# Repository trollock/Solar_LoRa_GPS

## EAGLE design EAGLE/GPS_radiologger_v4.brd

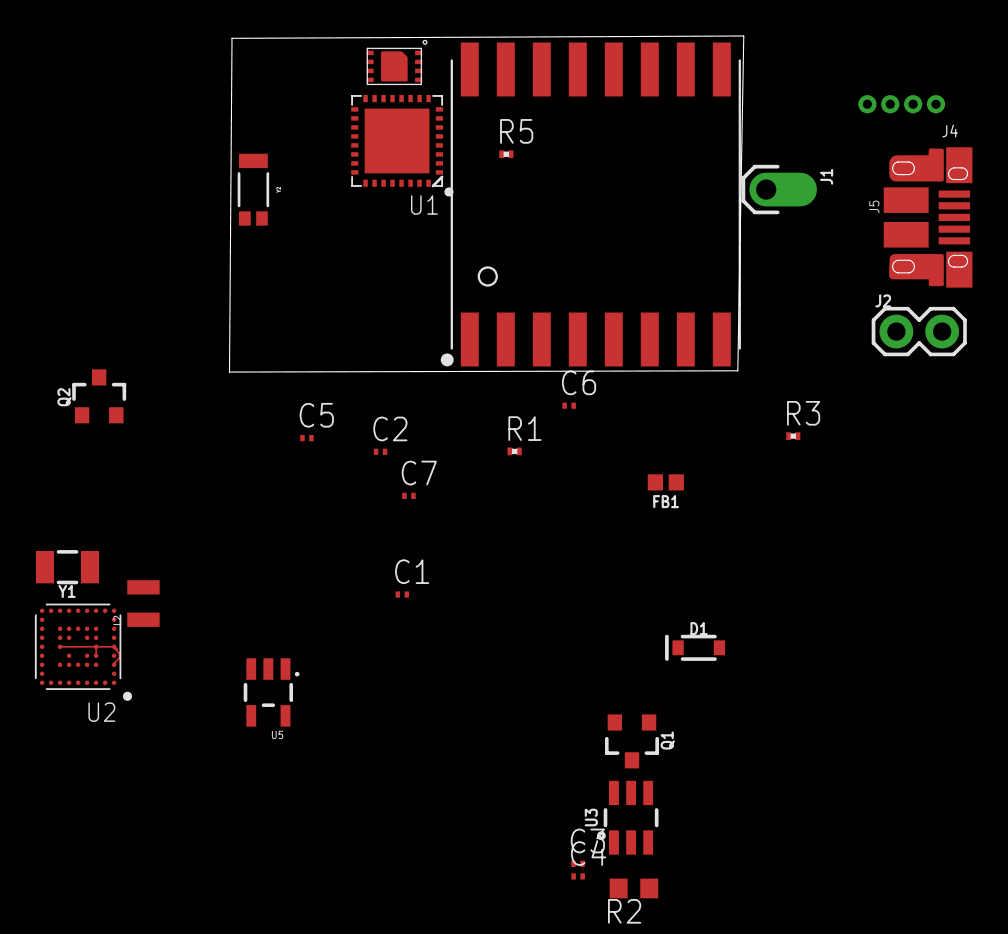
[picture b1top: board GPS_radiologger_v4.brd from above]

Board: 2 copper layers, 28 parts (0 on the bottom side), 30 nets.

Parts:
C1: 47 pF; C0201
C2, C3, C4: 10 uF; C0201
C5: 4.7 uF; C0201
C6: 0.1 uF; C0201
C7: 1 uF; C0201
D1: 1A/23V/620mV; SOD-323
FB1: FERRITE_BEAD-120_OHM-0402; 0402
J1: 1X01_OFFSET
J2: 1X02
J4: 1X04_1.27MM_NO_SILK
J5: USB-MICROB-PTH-MILL
L2: 2.2uH; 0806
Q1: 1.1A/60V/600mΩ; SOT23-3
Q2: 3.1A/30V/105mΩ; SOT23-3
R1: 10; R0201
R2: 30 k; R0603
R3, R5: 10k; R0201
U1: ATSAMD21E18A-U; QFN-32_SAMD
U2: UBLOX_ZOE_M8-0-10
U3: TPL5110; SOT23-6
U4: RFM95W; RFM95/96/97/98W
U5: 3.3V; SOT23-5
U$2: MB85RC64TA; 8-SON_2X3
Y1: 32.768kHz; CRYSTAL-SMD-3.2X1.5MM
Y2: W3011

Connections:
3.3V: C3.1, C6.1, Q1.3, R1.2, R5.2, U1.VDD, U1.VDDIN, U2.24, U2.25, U4.3.3V, U$2.P$5
!RESET: J4.1, U2.20
ANT: FB1.1, U2.4, Y2.1
D+: J5.D+, U1.PA25
D-: J5.D-, U1.PA24
DELAY/M_DRIVE: R2.1, U3.3
DONE: U1.PA22, U3.4
DRIVE: Q1.1, U3.5
GND: C1.2, C2.2, C3.2, C4.2, C5.2, C6.2, C7.2, J4.2, J5.GND, J5.SHIELD, J5.SHIELD2, J5.SHIELD3, J5.SHIELD4, J5.SHIELD5, J5.SHIELD6, J5.SHIELD7, J5.SHIELD8, J5.SHIELD9, J5.SHIELD10, R2.2, R3.1, U1.GND, U1.GNDANA, U1.PAD, U2.1, U2.3, U2.5, U2.7, U2.8, U2.9, U2.10, U2.11, U2.12, U2.17, U2.23, U2.29, U2.31, U2.37, U2.38, U2.39, U2.40, U2.41, U2.44, U2.46, U2.47, U2.49, U3.2, U4.GND@1, U4.GND@2, U4.GND@3, U5.2, U$2.P$1, U$2.P$2, U$2.P$3, U$2.P$4, U$2.P$9, Y2.2, Y2.3
MISO: U1.PA05, U4.MISO
MOSI: U1.PA06, U4.MOSI
unnamed: L2.2, U2.26
unnamed: C1.1, FB1.2, R1.1
unnamed: C4.1, U1.VDDCORE
unnamed: C5.1, L2.1, U2.27
unnamed: U2.18, Y1.P$2
unnamed: U2.19, Y1.P$1
RFM_ANT: J1.1, U4.ANT
RFM_CS: R5.1, U1.PA00, U4.NSS
RFM_INT: U1.PA01, U4.DIO0
RFM_RST: U1.PA04, U4.!RESET
SCK: U1.PA07, U4.SCK
SCL: U1.PA09, U2.32, U$2.P$7
SDA: U1.PA08, U2.2, U$2.P$8
SWCLK: J4.3, U1.PA30
SWDIO: J4.4, U1.PA31
VDD: C2.1, C7.1, Q1.2, U3.1, U3.6, U5.5
VIN: D1.C, Q2.2, U5.1, U5.3
V_BATT: J2.2, Q2.3, U2.16
V_USB: D1.A, J2.1, J5.VBUS, Q2.1, R3.2

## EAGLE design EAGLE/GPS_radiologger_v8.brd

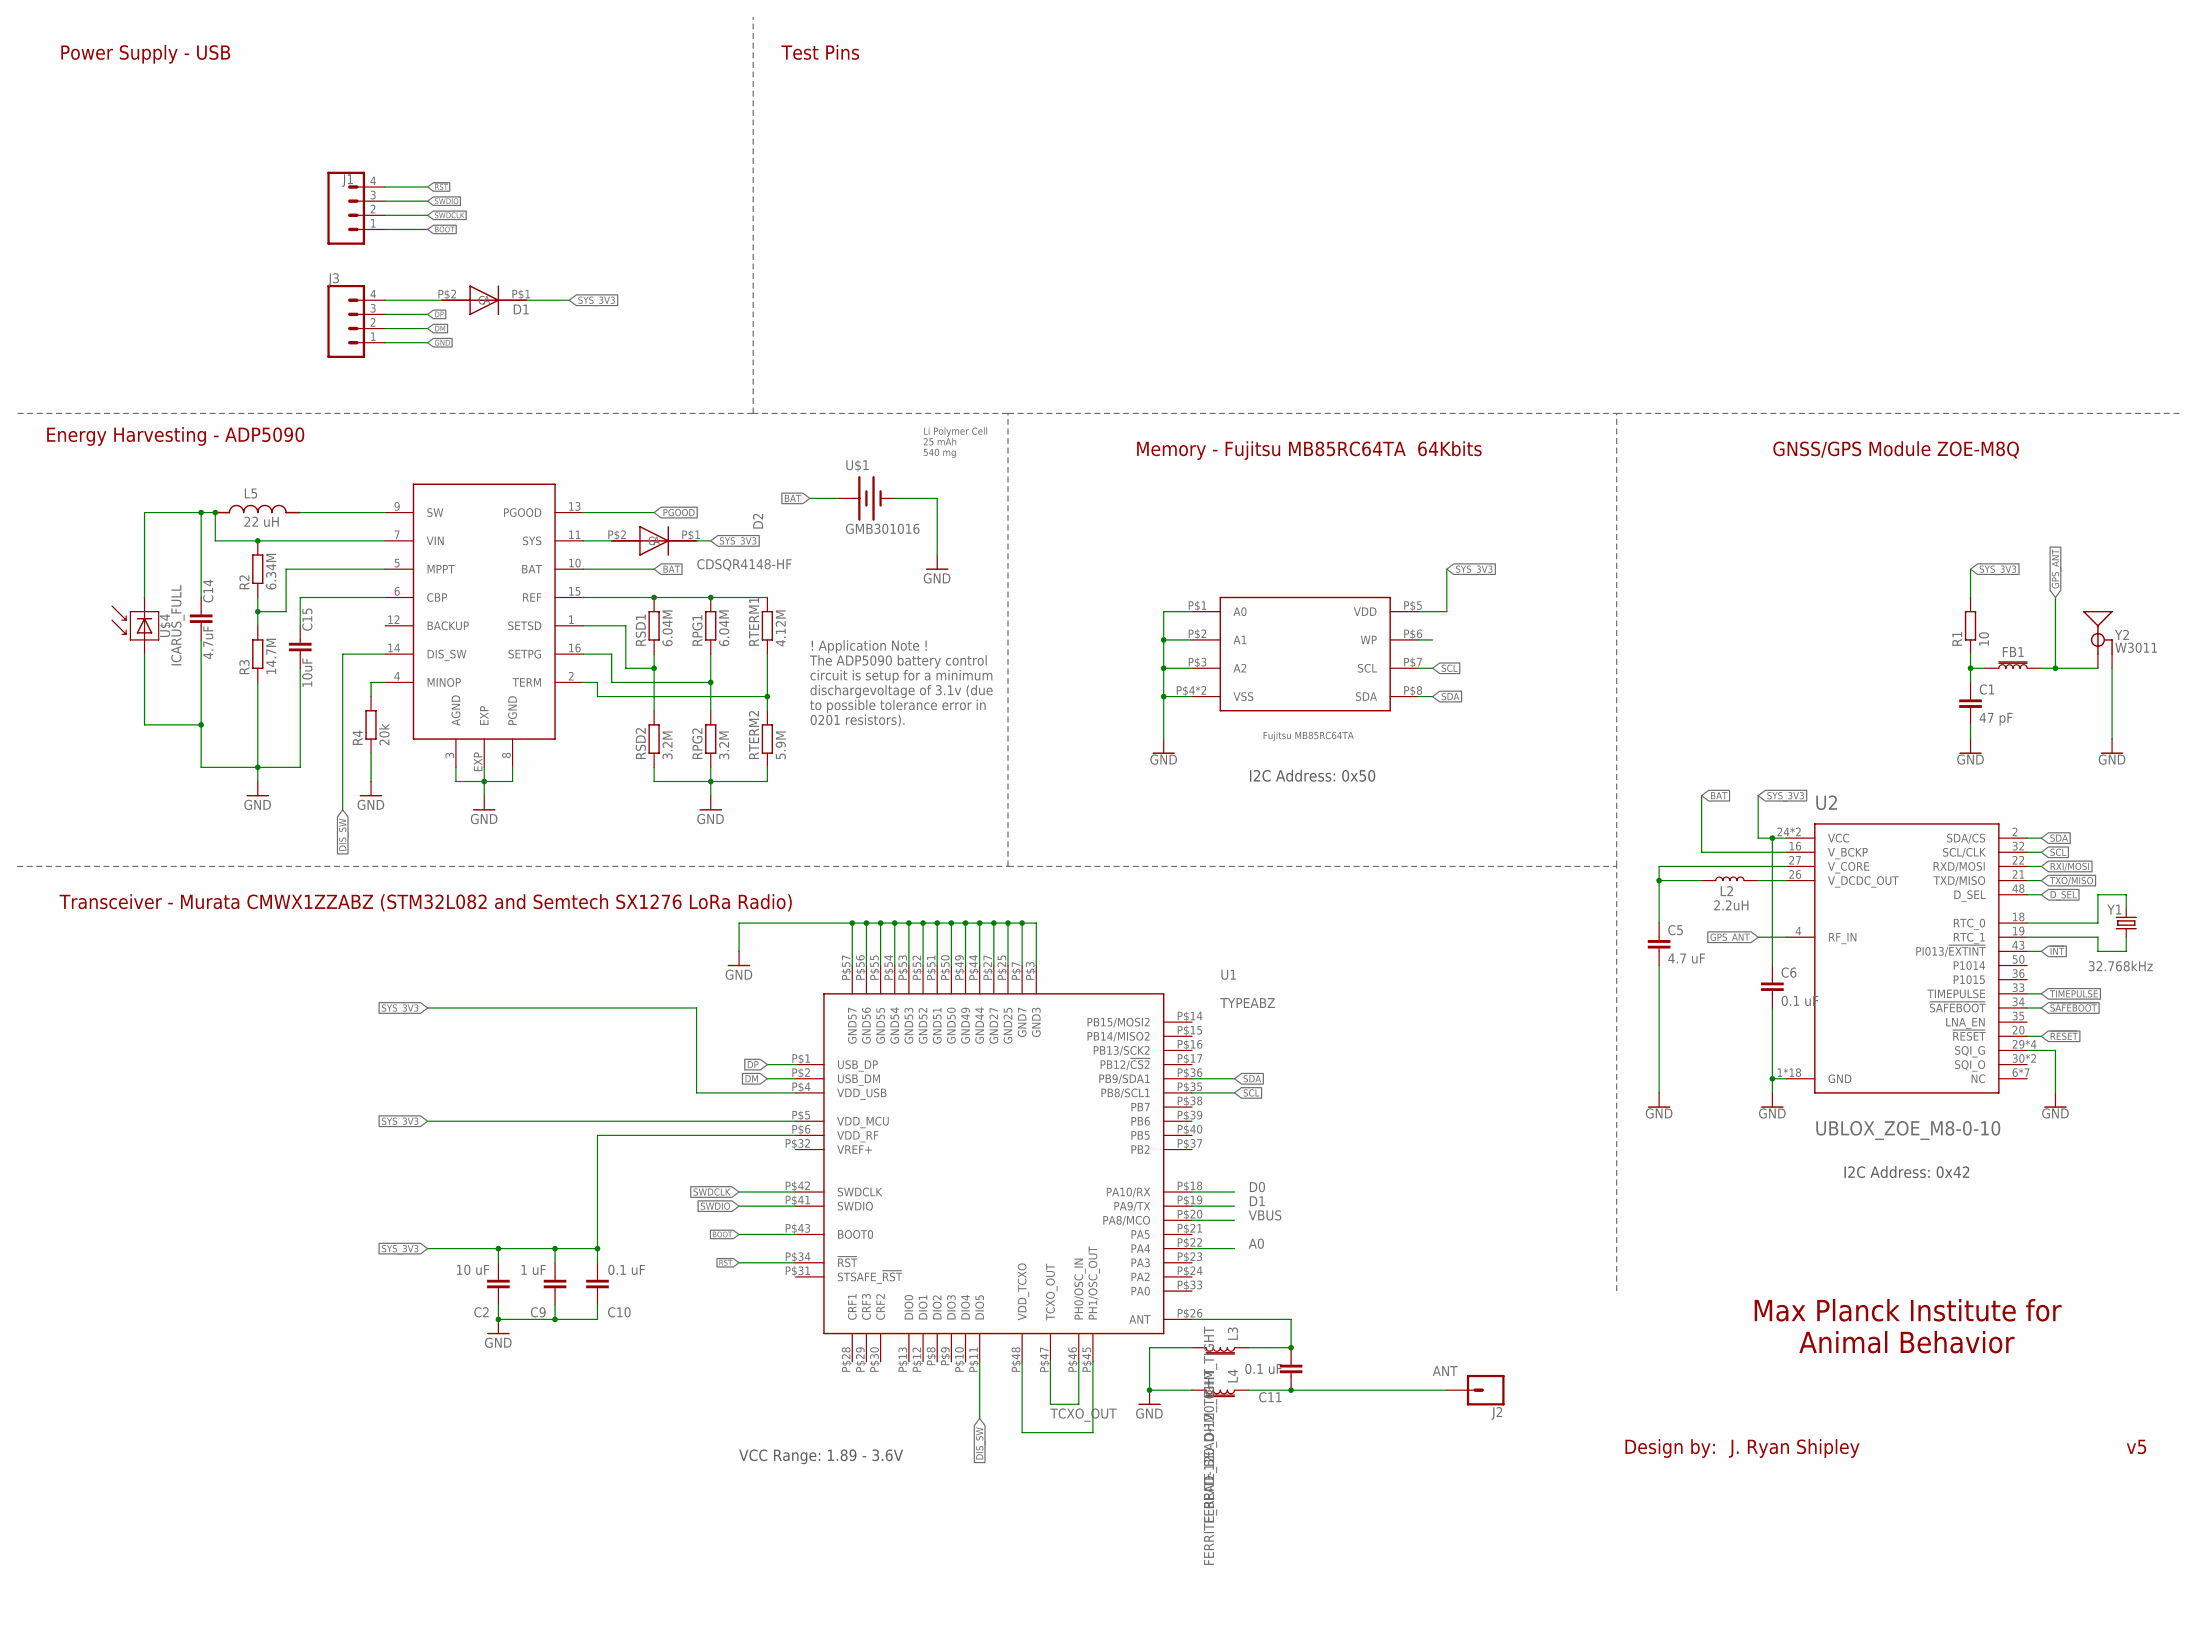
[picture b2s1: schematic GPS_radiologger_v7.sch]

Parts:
C1: 47 pF; C0201
C2: 10 uF; C0201
C5: 4.7 uF; C0201
C6, C10, C11: 0.1 uF; C0201
C9: 1 uF; C0201
C14: 4.7uF; C0201
C15: 10uF; C0402
D1, D2: CDSQR4148-HF
FB1: FERRITE_BEAD-120_OHM_TIGHT; 0402-TIGHT
J1, J3: CONN_041.27MM_NO_SILK; 1X04_1.27MM_NO_SILK
J2: CONN_01PTH_NO_SILK_SMALL; 1X01_SMALL
L2: 2.2uH; 0806
L3, L4: FERRITE_BEAD-120_OHM_TIGHT; 0402-TIGHT
L5: 22 uH; IND_LPS4012-103MRB
R1: 10; R0201
R2: 6.34M; R0201
R3: 14.7M; R0201
R4: 20k; R0201
RPG1: 6.04M; R0201
RPG2: 3.2M; R0201
RSD1: 6.04M; R0201
RSD2: 3.2M; R0201
RTERM1: 4.12M; R0201
RTERM2: 5.9M; R0201
U1: TYPEABZ
U2: UBLOX_ZOE_M8-0-10
U$1: GMB301016
U$2: MB85RC64TA; 8-SON_2X3
U$3: ADP5090; LFCSP-16-3X3
U$4: ICARUS_FULL
Y1: 32.768kHz; CRYSTAL-SMD-3.2X1.5MM
Y2: W3011

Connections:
!INT: U2.43 (PI013/!EXTINT)
!RESET: U2.20 (!RESET)
!RST: J1.4, U1.P$34 (!RST)
!SAFEBOOT: U2.34 (!SAFEBOOT)
A0: U1.P$22 (PA4)
ANT: C11.1, J2.P$1, L4.1
BAT: U2.16 (V_BCKP), U$1.+, U$3.10 (BAT)
D0: U1.P$18 (PA10/RX)
D1: U1.P$19 (PA9/TX)
DIS_SW: U1.P$11 (DIO5), U$3.14 (DIS_SW)
DM: J3.2, U1.P$2 (USB_DM)
DP: J3.3, U1.P$1 (USB_DP)
D_SEL: U2.48 (D_SEL)
GPS_ANT: FB1.1, U2.4 (RF_IN), Y2.1 (SIGNAL)
unnamed: U1.P$45 (PH1/OSC_OUT), U1.P$48 (VDD_TCXO)
unnamed: D2.P$2 (A), U$3.11 (SYS)
unnamed: L2.2, U2.26 (V_DCDC_OUT)
unnamed: L5.2, U$3.9 (SW)
unnamed: U$3.3 (AGND), U$3.8 (PGND), U$3.EXP
unnamed: R2.1, R3.2, U$3.5 (MPPT)
unnamed: C15.1, U$3.6 (CBP)
unnamed: C1.1, FB1.2, R1.1
unnamed: R4.2, U$3.4 (MINOP)
unnamed: RTERM1.1, RTERM2.2, U$3.2 (TERM)
unnamed: RPG1.1, RPG2.2, U$3.16 (SETPG)
unnamed: C5.1, L2.1, U2.27 (V_CORE)
unnamed: U2.18 (RTC_0), Y1.P$2 (2)
unnamed: U2.19 (RTC_1), Y1.P$1 (1)
unnamed: RSD1.1, RSD2.2, U$3.1 (SETSD)
unnamed: RPG1.2, RSD1.2, RTERM1.2, U$3.15 (REF)
unnamed: D1.P$2 (A), J3.4
unnamed: C11.2, L3.1, U1.P$26 (ANT)
PGOOD: U$3.13 (PGOOD)
RXI/MOSI: U2.22 (RXD/MOSI)
SCL: U1.P$35 (PB8/SCL1), U2.32 (SCL/CLK), U$2.P$7 (SCL)
SDA: U1.P$36 (PB9/SDA1), U2.2 (SDA/CS), U$2.P$8 (SDA)
SWDIO: J1.3, U1.P$41 (SWDIO)
SYS_3V3: C2.2, C6.1, C9.2, C10.2, D1.P$1 (C), D2.P$1 (C), R1.2, U1.P$4 (VDD_USB), U1.P$5 (VDD_MCU), U1.P$6 (VDD_RF), U2.24 (VCC), U2.25 (VCC), U$2.P$5 (VDD)
TCXO_OUT: U1.P$46 (PH0/OSC_IN), U1.P$47 (TCXO_OUT)
TIMEPULSE: U2.33 (TIMEPULSE)
TXO/MISO: U2.21 (TXD/MISO)
VBUS: U1.P$20 (PA8/MCO)
VIN: C14.1, L5.1, R2.2, U$3.7 (VIN), U$4.P$1 (PLUS)
VREF+: U1.P$32 (VREF+)

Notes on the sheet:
GNSS/GPS Module ZOE-M8Q
VCC Range: 1.89 - 3.6V
I2C Address: 0x42
Max Planck Institute for Animal Behavior
Transceiver - Murata CMWX1ZZABZ (STM32L082 and Semtech SX1276 LoRa Radio)
Power Supply - USB
Energy Harvesting - ADP5090
I2C Address: 0x50
Memory - Fujitsu MB85RC64TA 64Kbits
Design by:
J. Ryan Shipley
Li Polymer Cell 25 mAh 540 mg
Test Pins
! Application Note ! The ADP5090 battery control circuit is setup for a minimum dischargevoltage of 3.1v (due to possible tolerance error in 0201 resistors).

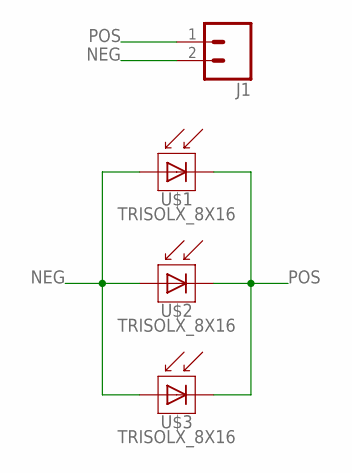
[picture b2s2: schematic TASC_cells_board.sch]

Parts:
J1: CONN_02; 1X02
U$1, U$2, U$3: TRISOLX_8X16

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
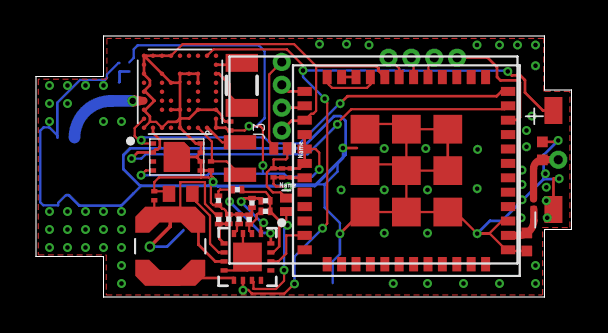
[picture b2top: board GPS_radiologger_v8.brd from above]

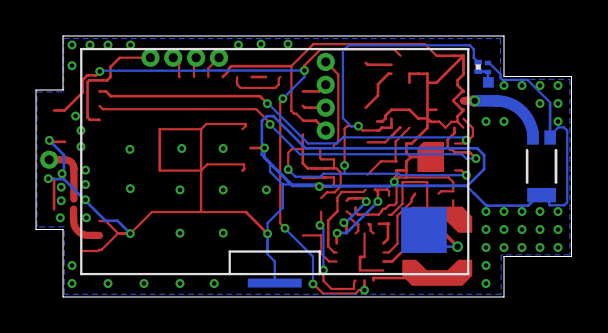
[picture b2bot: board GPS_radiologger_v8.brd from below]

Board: 2 copper layers, 29.8 x 14.5 mm, 37 parts (5 on the bottom side), 34 nets.

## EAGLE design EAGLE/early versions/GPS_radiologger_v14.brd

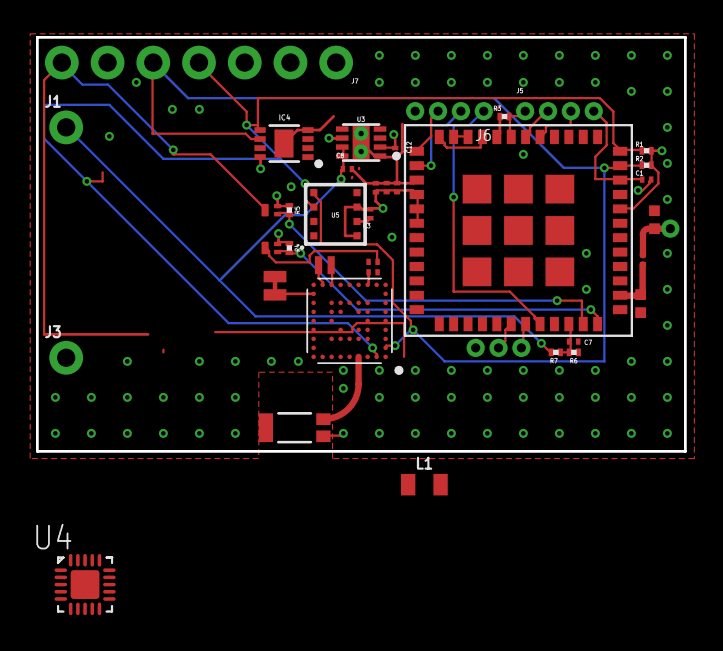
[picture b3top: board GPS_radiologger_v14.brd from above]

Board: 4 copper layers, 36.0 x 23.0 mm, 39 parts (0 on the bottom side), 28 nets.

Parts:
C1, C3, C6, C7, C10, C11: 0.1 uF; C0201
C2, C12: 10 uF; C0201
C5, C8: 4.7 uF; C0201
C9: 1 uF; C0201
IC4: CAT24M01HU5I-GT3; SON50P300X200X55-9N
J1, J3: 1X01_NO_SILK
J2: 1X01_SMALL
J4: 1X03_1.27MM_NO_SILK
J5, J6: 1X04_1.27MM_NO_SILK
J7: 1X07_NO_SILK
JP1: JUMPER-SMT_2_NC_TRACE_NO-SILK; SMT-JUMPER_2_NC_TRACE_NO-SILK
L1: 2.2µH/< 0.2 ohm /500mA; 0805
L3, L4: FERRITE_BEAD-120_OHM_TIGHT; 0402-TIGHT
PDTA143TMB,1, PDTA143TMB,315: TINYPICO-PNPAMB; SOT883(B)
R1, R2: 4.7 k; R0201
R3: 10k; R0201
R4, R5: 100k; R0201
R6: 10 M; R0201
R7: 4.7 M; R0201
U1: TYPEABZ
U2: UBLOX_ZOE_M8-0-10
U3: MICROCHIP_MCP1810T-33I-J8AMICROCHIP_MCP1810T-33I-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; MICROCHIP_MCP1810T-33I-J8A_0
U4: SPV1050
U5: BME680BME680; LGA3.0X3.0
Y1: 32.768kHz; CRYSTAL-SMD-1.0X1.2MM
Y2: W3011

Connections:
ANT: C11.1, J2.P$1, L4.1
BAT: C8.1, J1.1, R7.2, U3.7, U3.8
BOOT: J5.1, R3.2, U1.P$43
DM: J6.2, U1.P$2
DP: J6.3, U1.P$1
GND: C1.2, C2.1, C3.2, C5.2, C6.2, C7.2, C8.2, C9.1, C10.1, C12.2, IC4.4, IC4.9, J3.1, J6.4, J7.1, J7.6, L3.2, L4.2, R3.1, R6.1, U1.P$3, U1.P$7, U1.P$25, U1.P$27, U1.P$44, U1.P$49, U1.P$50, U1.P$51, U1.P$52, U1.P$53, U1.P$54, U1.P$55, U1.P$56, U1.P$57, U2.1, U2.3, U2.5, U2.7, U2.8, U2.9, U2.10, U2.11, U2.12, U2.17, U2.23, U2.29, U2.31, U2.37, U2.38, U2.39, U2.40, U2.41, U2.44, U2.46, U2.47, U2.49, U3.1, U3.9, U5.1, U5.5, U5.7, Y2.2, Y2.3
GPS_ANT: U2.4, Y2.1
unnamed: U1.P$45, U1.P$48
unnamed: JP1.2, U2.16
unnamed: C5.1, L1.1, U2.27
unnamed: L1.2, U2.26
unnamed: U2.18, Y1.P$2
unnamed: U2.19, Y1.P$1
unnamed: C11.2, L3.1, U1.P$26
POWER: C2.2, C3.1, C6.1, C9.2, C10.2, C12.1, IC4.8, J4.1, JP1.1, PDTA143TMB,1.2, PDTA143TMB,315.2, R1.2, R2.2, R4.2, R5.2, U1.P$4, U1.P$5, U1.P$6, U1.P$32, U2.24, U2.25, U3.2, U3.6, U5.6, U5.8
RST: C1.1, J5.4, U1.P$34
RX: J4.2, U1.P$18
SCD_PDTA: PDTA143TMB,1.1, R5.1, U1.P$23
SCD_PWR: J7.7, PDTA143TMB,1.3
SCL: IC4.6, J7.5, R2.1, U1.P$35, U2.32, U5.4
SDA: IC4.5, J7.4, R1.1, U1.P$36, U2.2, U5.3
SWDCLK: J5.2, U1.P$42
SWDIO: J5.3, U1.P$41
TCXO_OUT: U1.P$46, U1.P$47
TX: J4.3, U1.P$19
VBUS: J6.1, U1.P$20
VOLT_MEAS: C7.1, R6.2, R7.1, U1.P$22
ZOE_PDTA: PDTA143TMB,315.1, R4.1, U1.P$24

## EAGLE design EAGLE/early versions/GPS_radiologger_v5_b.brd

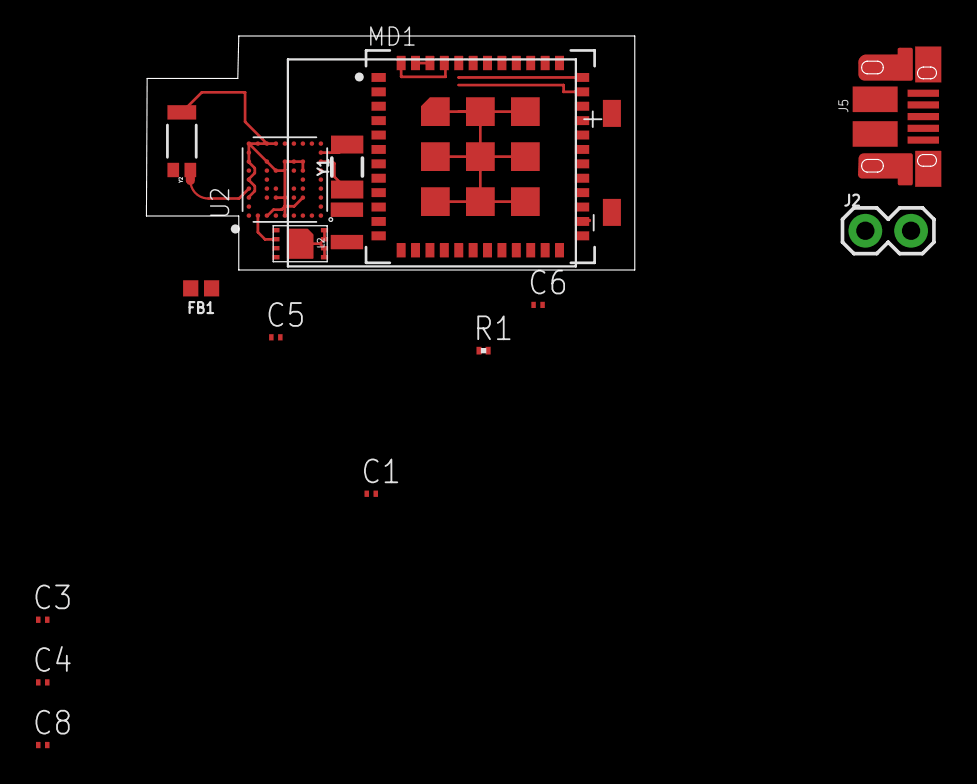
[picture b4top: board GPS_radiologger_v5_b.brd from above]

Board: 2 copper layers, 17 parts (0 on the bottom side), 15 nets.

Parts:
C1: 47 pF; C0201
C3: 0.1uF; C0201
C4: 1uF; C0201
C5: 4.7 uF; C0201
C6: 0.1 uF; C0201
C8: 10uF; C0201
FB1: FERRITE_BEAD-120_OHM-0402; 0402
J2: 1X02
J5: USB-MICROB-PTH-MILL
L2: 2.2uH; 0806
MD1: MURATA_CMWX1ZZABZ-078MURATA_CMWX1ZZABZ-078_0_0; MURATA_CMWX1ZZABZ-078_0
R1: 10; R0201
U2: UBLOX_ZOE_M8-0-10
U$1: GMB301016
U$2: MB85RC64TA; 8-SON_2X3
Y1: 32.768kHz; CRYSTAL-SMD-3.2X1.5MM
Y2: W3011

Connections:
3.3V: R1.2, U$2.P$5
3V3: C3.1, C4.1, C8.1, MD1.4, MD1.5, MD1.6
GND: C1.2, C3.2, C4.2, C5.2, C6.2, C8.2, J5.GND, J5.SHIELD, J5.SHIELD2, J5.SHIELD3, J5.SHIELD4, J5.SHIELD5, J5.SHIELD6, J5.SHIELD7, J5.SHIELD8, J5.SHIELD9, J5.SHIELD10, MD1.3, MD1.7, MD1.25, MD1.27, MD1.44, MD1.49, MD1.50, MD1.51, MD1.52, MD1.53, MD1.54, MD1.55, MD1.56, MD1.57, U2.1, U2.3, U2.5, U2.7, U2.8, U2.9, U2.10, U2.11, U2.12, U2.17, U2.23, U2.29, U2.31, U2.37, U2.38, U2.39, U2.40, U2.41, U2.44, U2.46, U2.47, U2.49, U$2.P$1, U$2.P$2, U$2.P$3, U$2.P$4, U$2.P$9, Y2.2, Y2.3
GPS_ANT: FB1.1, U2.4, Y2.1
GPS_V: C6.1, U2.24, U2.25
unnamed: L2.2, U2.26
unnamed: MD1.46, MD1.47
unnamed: C1.1, FB1.2, R1.1
unnamed: C5.1, L2.1, U2.27
unnamed: U2.18, Y1.P$2
unnamed: U2.19, Y1.P$1
SCL: MD1.35, U2.32, U$2.P$7
SDA: MD1.36, U2.2, U$2.P$8
TXCO: MD1.45, MD1.48
V_USB: J2.1, J5.VBUS

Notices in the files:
parts and their libraries:
SparkFun-IC-Power: Licensing: Creative Commons ShareAlike 4.0 International - https://creativecommons.org/licenses/by-sa/4.0
